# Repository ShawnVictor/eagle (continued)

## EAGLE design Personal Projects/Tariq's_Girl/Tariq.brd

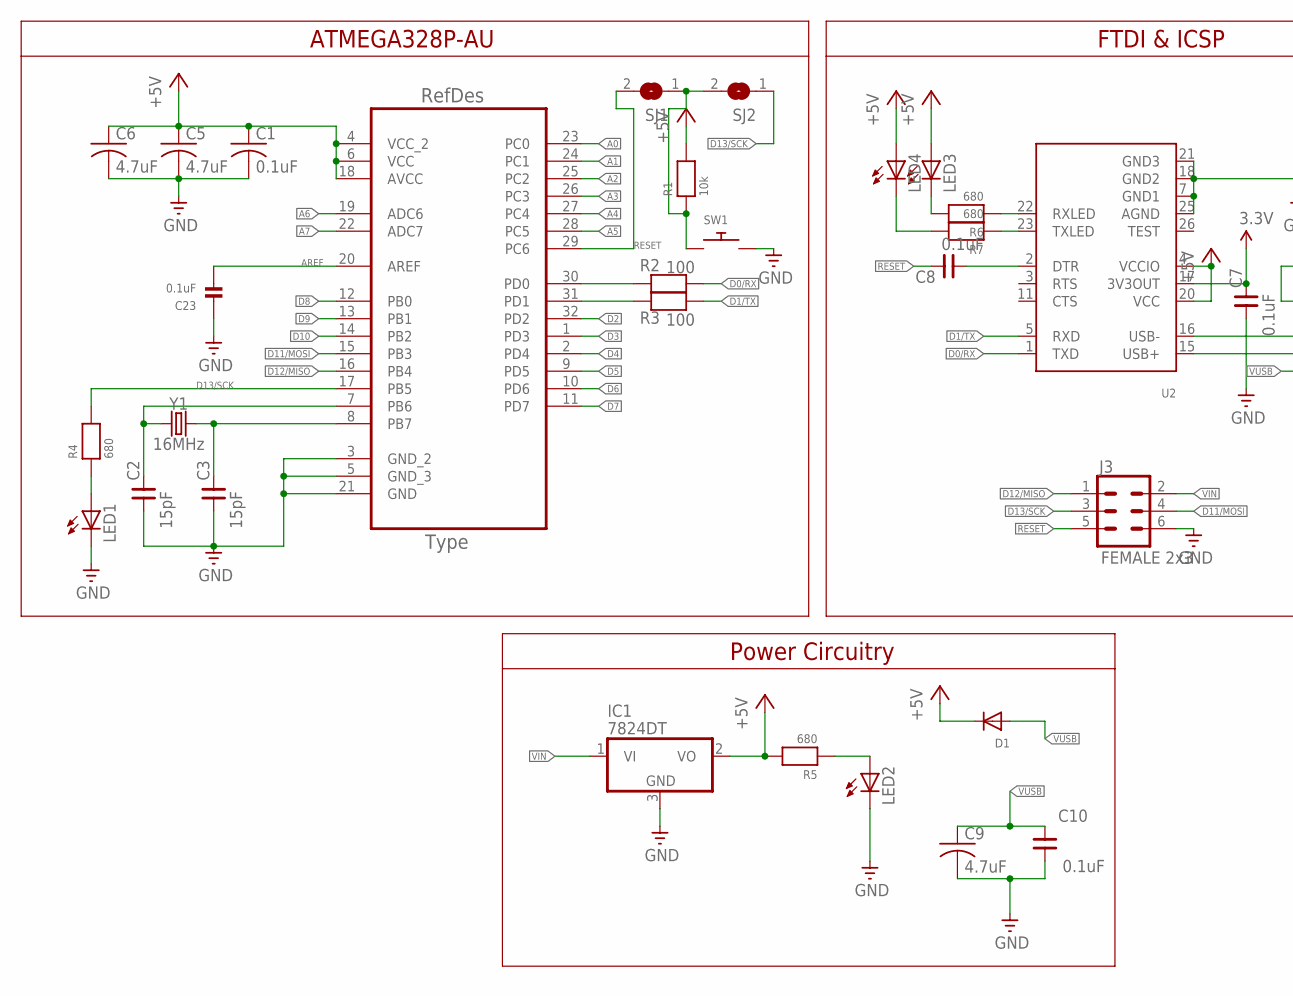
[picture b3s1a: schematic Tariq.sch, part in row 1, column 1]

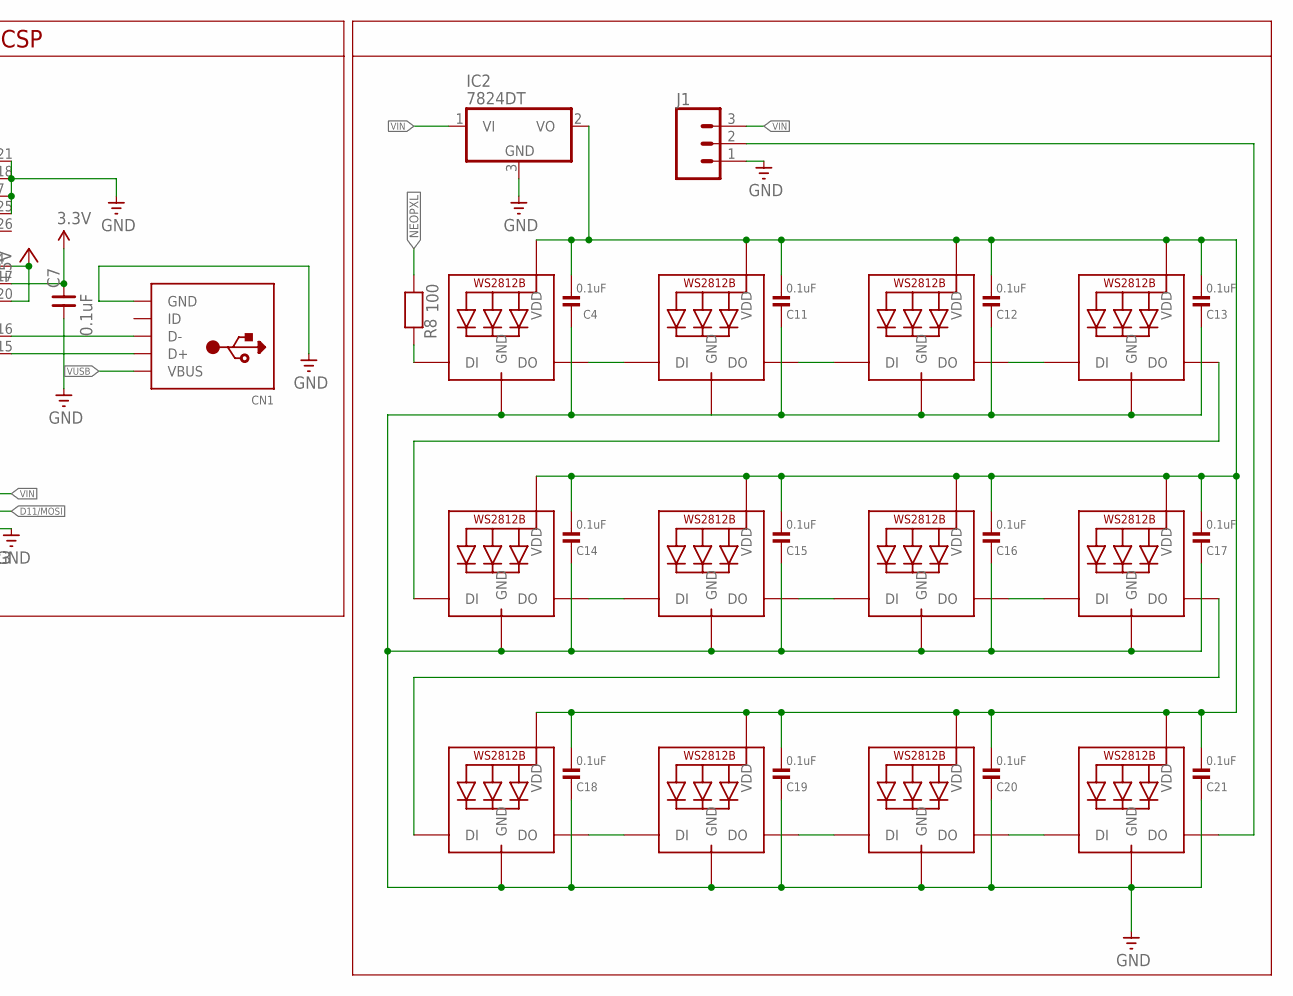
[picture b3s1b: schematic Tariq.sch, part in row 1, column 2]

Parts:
C1: 0.1uF; C0805
C2, C3: 15pF; 0805
C4, C11, C12, C13, C14, C15, C16, C17, C18, C19, C20, C21, C23: 0.1uF; 0603
C5, C6, C9: 4.7uF; C0805
C7, C8, C10: 0.1uF; 0805
CN1: USBMINIB; USB-MINIB
D1: DIODESOD-123; SOD-123
IC1, IC2: 7824DT; TO252
J1: CONN_03; 1X03
J3: FEMALE 2x3; 2X3
LED1, LED2, LED3, LED4: LEDCHIPLED_0805; CHIPLED_0805
LED5, LED6, LED7, LED8, LED9, LED10, LED11, LED12, LED13, LED14, LED15, LED16: WS2812B5050; WS2812B
R1: 10k; 0603
R2, R3, R8: 100; 0603
R4, R5, R6, R7: 680; 0603
SJ1, SJ2: SOLDERJUMPERWAVE; SOLDERJUMPER_WAVE
SW1: SWITCH_PUSHBUTTONEVQ-PE; TACT_PANA-EVQ
U1: ATMEGA328P-AU; QFP80P900X900X120-32N
U2: FT232RLSSOP28; SSOP28DB
Y1: 16MHz; HC49US

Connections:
3.3V: C7.2, U2.17 (3V3OUT)
+5V: C1.1, C5.1, C6.1, D1.C, IC1.2 (VO), LED3.A, LED4.A, R1.2, R5.2, U1.4 (VCC_2), U1.6 (VCC), U1.18 (AVCC), U2.4 (VCCIO), U2.20 (VCC)
A0: U1.23 (PC0)
A1: U1.24 (PC1)
A2: U1.25 (PC2)
A3: U1.26 (PC3)
A4: U1.27 (PC4)
A5: U1.28 (PC5)
A6: U1.19 (ADC6)
A7: U1.22 (ADC7)
AREF: C23.2, U1.20 (AREF)
D0/RX: R2.1, U2.1 (TXD)
D1/TX: R3.1, U2.5 (RXD)
D2: U1.32 (PD2)
D3: U1.1 (PD3)
D4: U1.2 (PD4)
D5: U1.9 (PD5)
D6: U1.10 (PD6)
D7: U1.11 (PD7)
D8: U1.12 (PB0)
D9: U1.13 (PB1)
D10: U1.14 (PB2)
D11/MOSI: J3.4, U1.15 (PB3)
D12/MISO: J3.1, U1.16 (PB4)
D13/SCK: J3.3, R4.2, SJ2.1, U1.17 (PB5)
GND: C1.2, C2.1, C3.1, C4.1, C5.2, C6.2, C7.1, C9.2, C10.1, C11.1, C12.1, C13.1, C14.1, C15.1, C16.1, C17.1, C18.1, C19.1, C20.1, C21.1, C23.1, CN1.GND, IC1.3 (GND), IC2.3 (GND), J1.1, J3.6, LED1.C, LED2.C, LED5.3-GND (GND), LED6.3-GND (GND), LED7.3-GND (GND), LED8.3-GND (GND), LED9.3-GND (GND), LED10.3-GND (GND), LED11.3-GND (GND), LED12.3-GND (GND), LED13.3-GND (GND), LED14.3-GND (GND), LED15.3-GND (GND), LED16.3-GND (GND), SW1.P$2, U1.3 (GND_2), U1.5 (GND_3), U1.21 (GND), U2.7 (GND1), U2.18 (GND2), U2.21 (GND3), U2.25 (AGND)
unnamed: C3.2, U1.8 (PB7), Y1.2
unnamed: C2.2, U1.7 (PB6), Y1.1
unnamed: LED2.A, R5.1
unnamed: CN1.D+, U2.15 (USB+)
unnamed: CN1.D-, U2.16 (USB-)
unnamed: R2.2, U1.30 (PD0)
unnamed: R3.2, U1.31 (PD1)
unnamed: LED3.C, R6.2
unnamed: LED1.A, R4.1
unnamed: LED5.2-DOUT (DO), LED6.4-DIN (DI)
unnamed: R6.1, U2.22 (RXLED)
unnamed: R7.1, U2.23 (TXLED)
unnamed: C8.1, U2.2 (DTR)
unnamed: LED4.C, R7.2
unnamed: LED6.2-DOUT (DO), LED7.4-DIN (DI)
unnamed: LED7.2-DOUT (DO), LED8.4-DIN (DI)
unnamed: LED8.2-DOUT (DO), LED9.4-DIN (DI)
unnamed: C4.2, C11.2, C12.2, C13.2, C14.2, C15.2, C16.2, C17.2, C18.2, C19.2, C20.2, C21.2, IC2.2 (VO), LED5.1-VDD (VDD), LED6.1-VDD (VDD), LED7.1-VDD (VDD), LED8.1-VDD (VDD), LED9.1-VDD (VDD), LED10.1-VDD (VDD), LED11.1-VDD (VDD), LED12.1-VDD (VDD), LED13.1-VDD (VDD), LED14.1-VDD (VDD), LED15.1-VDD (VDD), LED16.1-VDD (VDD)
unnamed: LED9.2-DOUT (DO), LED10.4-DIN (DI)
unnamed: LED10.2-DOUT (DO), LED11.4-DIN (DI)
unnamed: LED11.2-DOUT (DO), LED12.4-DIN (DI)
unnamed: LED12.2-DOUT (DO), LED13.4-DIN (DI)
unnamed: LED13.2-DOUT (DO), LED14.4-DIN (DI)
unnamed: LED14.2-DOUT (DO), LED15.4-DIN (DI)
unnamed: LED15.2-DOUT (DO), LED16.4-DIN (DI)
unnamed: LED5.4-DIN (DI), R8.2
unnamed: J1.2, LED16.2-DOUT (DO)
unnamed: R1.1, SJ1.1, SJ2.2, SW1.P$1
NEOPXL: R8.1
RESET: C8.2, J3.5, SJ1.2, U1.29 (PC6)
VIN: IC1.1 (VI), IC2.1 (VI), J1.3, J3.2
VUSB: C9.1, C10.2, CN1.VBUS, D1.A

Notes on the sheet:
ATMEGA328P-AU
FTDI & ICSP
Power Circuitry

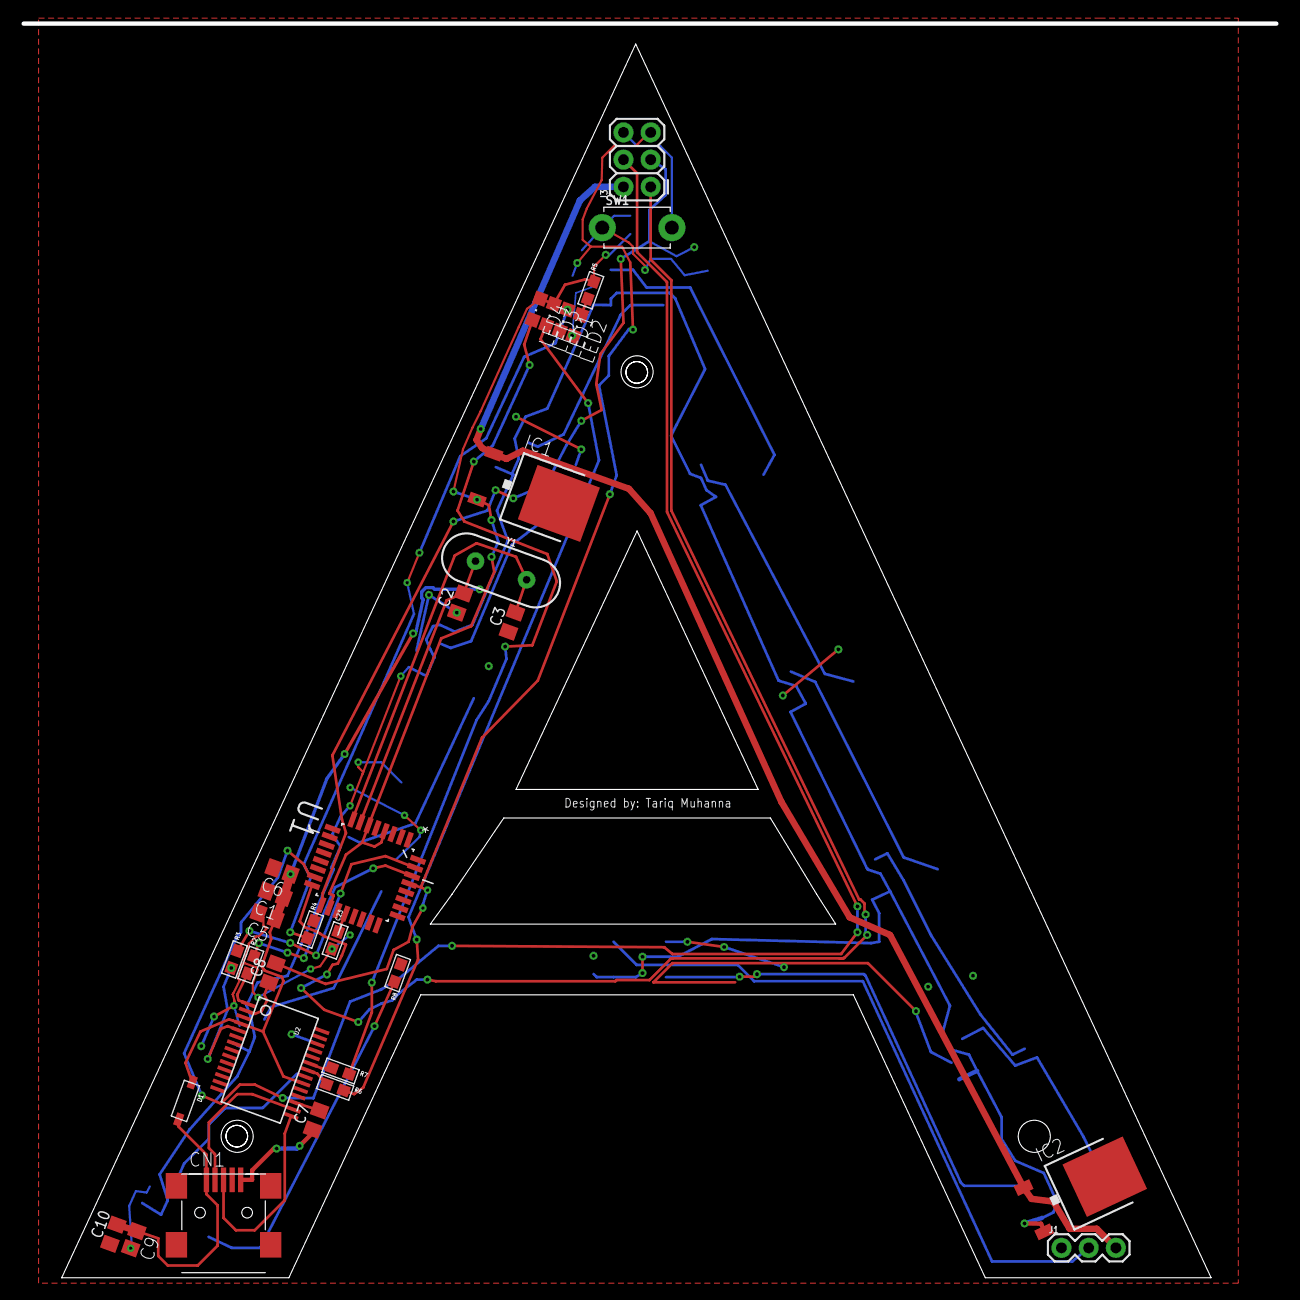
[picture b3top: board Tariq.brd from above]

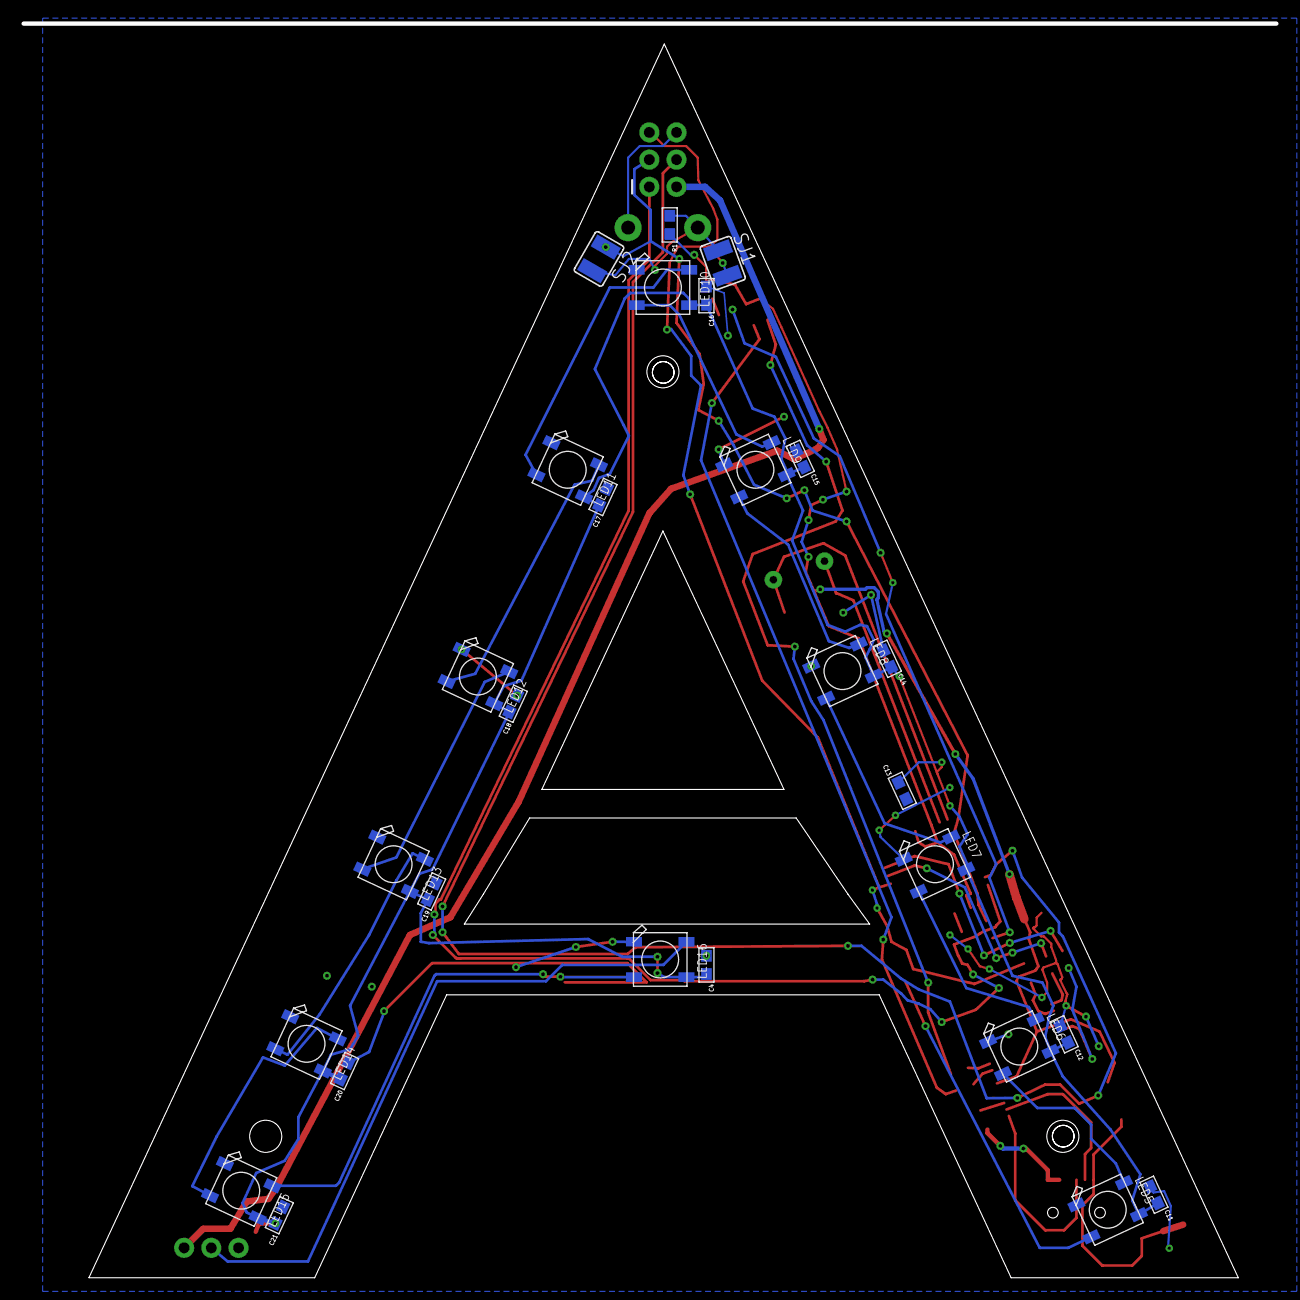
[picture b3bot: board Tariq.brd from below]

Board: 2 copper layers, 117.0 x 117.1 mm, 58 parts (27 on the bottom side), 40 nets.

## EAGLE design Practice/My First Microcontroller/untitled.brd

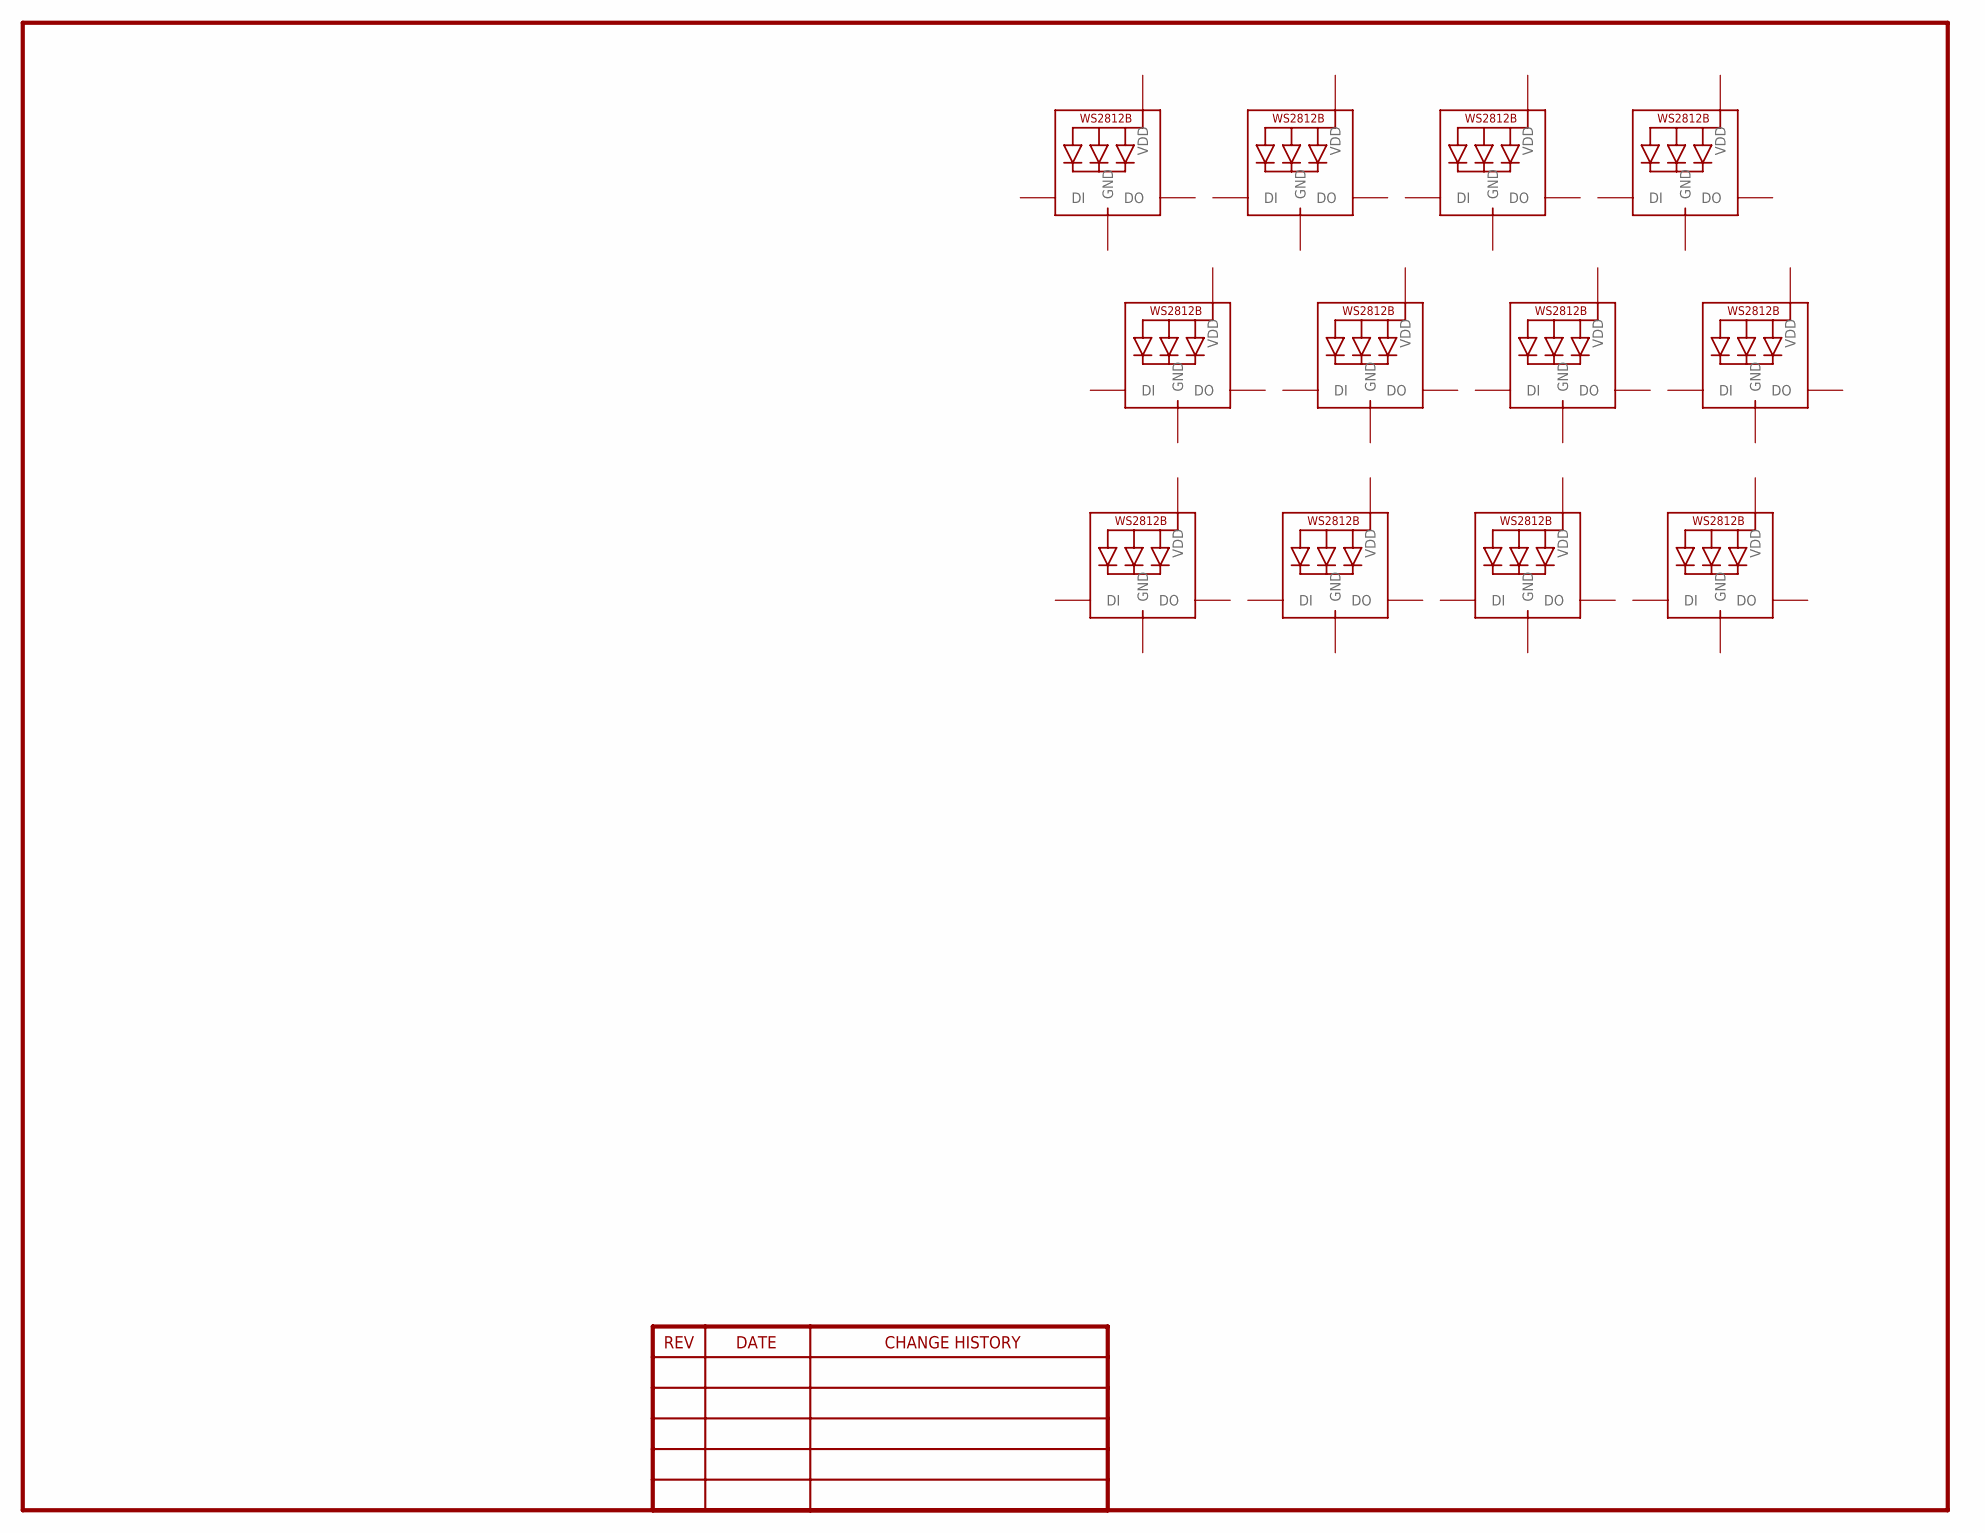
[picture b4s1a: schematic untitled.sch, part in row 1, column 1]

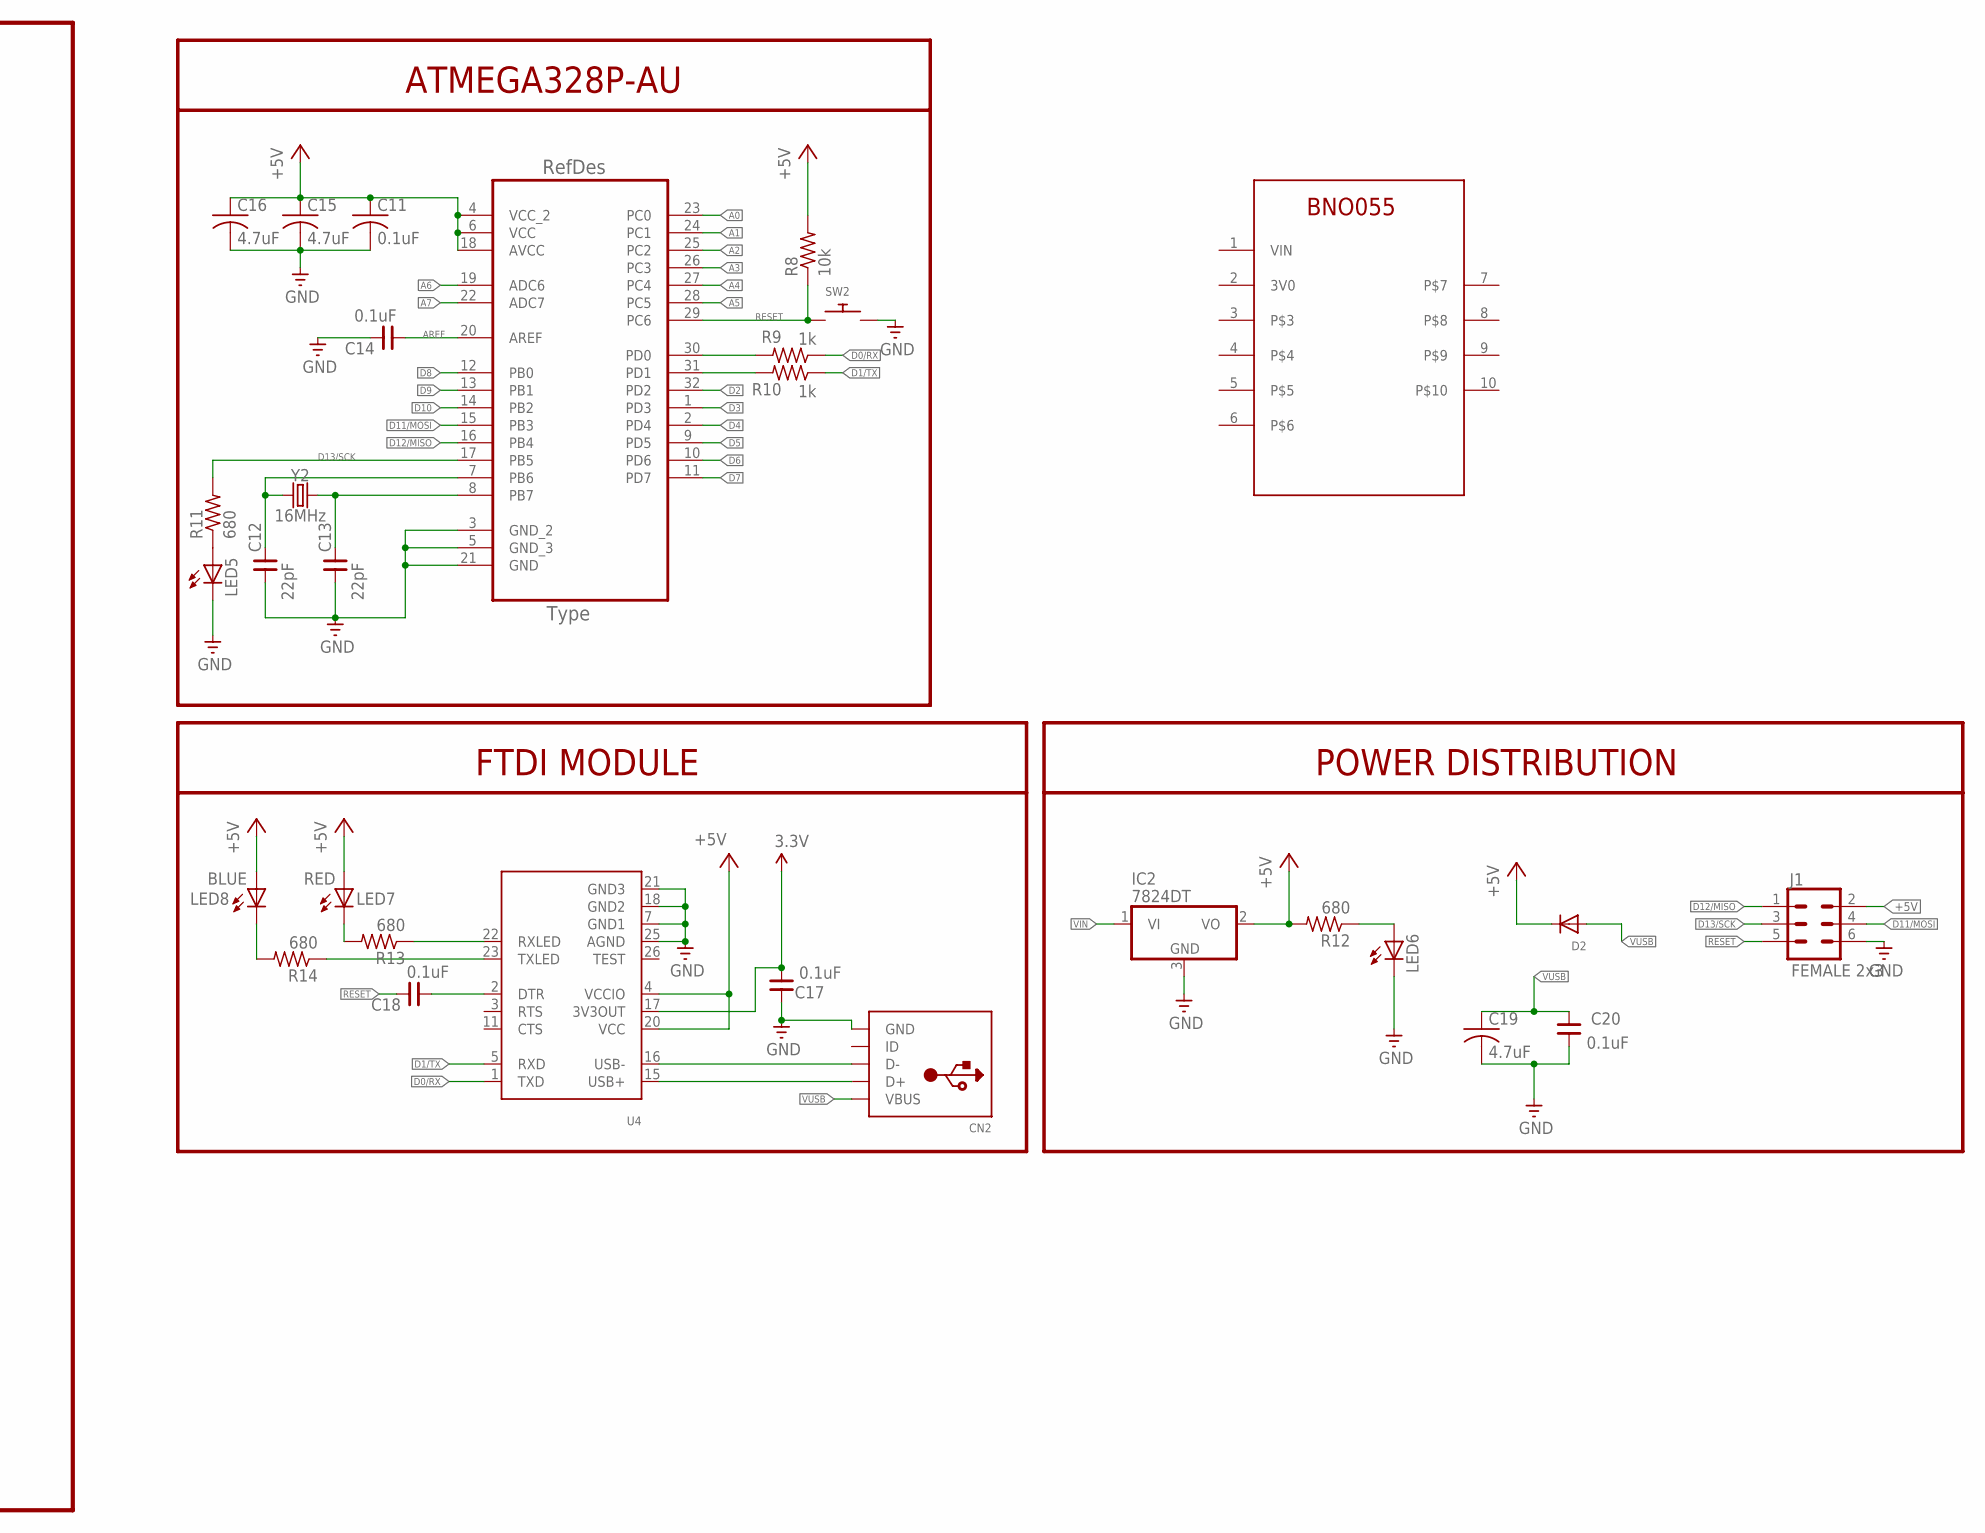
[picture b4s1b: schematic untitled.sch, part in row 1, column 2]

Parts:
C11: 0.1uF; C0805
C12, C13: 22pF; 0805
C14, C17, C18, C20: 0.1uF; 0805
C15, C16, C19: 4.7uF; C0805
CN2: USBMINIB; USB-MINIB
D2: DIODESOD-123; SOD-123
IC2: 7824DT; TO252
J1: FEMALE 2x3; 2X3
LED1, LED2, LED3, LED4, LED9, LED10, LED11, LED12, LED13, LED14, LED15, LED16: WS2812B5050; WS2812B
LED5, LED6: LEDCHIPLED_0805; CHIPLED_0805
LED7: RED; CHIPLED_0805
LED8: BLUE; CHIPLED_0805
R8: 10k; R0805
R9, R10: 1k; R0805
R11, R12, R13, R14: 680; R0805
SW2: SWITCH_PUSHBUTTONEVQ-PE; TACT_PANA-EVQ
U3: ATMEGA328P-AU; QFP80P900X900X120-32N
U4: FT232RLSSOP28; SSOP28DB
U$1: BNO055; BNO055_SHEILD
Y2: 16MHz; HC49US

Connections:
3.3V: C17.2, U4.17 (3V3OUT)
+5V: C11.1, C15.1, C16.1, D2.C, IC2.2 (VO), J1.2, LED7.A, LED8.A, R8.2, R12.2, U3.4 (VCC_2), U3.6 (VCC), U3.18 (AVCC), U4.4 (VCCIO), U4.20 (VCC)
A0: U3.23 (PC0)
A1: U3.24 (PC1)
A2: U3.25 (PC2)
A3: U3.26 (PC3)
A4: U3.27 (PC4)
A5: U3.28 (PC5)
A6: U3.19 (ADC6)
A7: U3.22 (ADC7)
AREF: C14.1, U3.20 (AREF)
D0/RX: R9.1, U4.1 (TXD)
D1/TX: R10.1, U4.5 (RXD)
D2: U3.32 (PD2)
D3: U3.1 (PD3)
D4: U3.2 (PD4)
D5: U3.9 (PD5)
D6: U3.10 (PD6)
D7: U3.11 (PD7)
D8: U3.12 (PB0)
D9: U3.13 (PB1)
D10: U3.14 (PB2)
D11/MOSI: J1.4, U3.15 (PB3)
D12/MISO: J1.1, U3.16 (PB4)
D13/SCK: J1.3, R11.2, U3.17 (PB5)
GND: C11.2, C12.1, C13.1, C14.2, C15.2, C16.2, C17.1, C19.2, C20.1, CN2.GND, IC2.3 (GND), J1.6, LED1.3-GND (GND), LED2.3-GND (GND), LED3.3-GND (GND), LED4.3-GND (GND), LED5.C, LED6.C, LED9.3-GND (GND), LED10.3-GND (GND), LED11.3-GND (GND), LED12.3-GND (GND), LED13.3-GND (GND), LED14.3-GND (GND), LED15.3-GND (GND), LED16.3-GND (GND), SW2.P$2, U3.3 (GND_2), U3.5 (GND_3), U3.21 (GND), U4.7 (GND1), U4.18 (GND2), U4.21 (GND3), U4.25 (AGND)
unnamed: LED5.A, R11.1
unnamed: C13.2, U3.8 (PB7), Y2.2
unnamed: C12.2, U3.7 (PB6), Y2.1
unnamed: R9.2, U3.30 (PD0)
unnamed: R10.2, U3.31 (PD1)
unnamed: LED6.A, R12.1
unnamed: CN2.D+, U4.15 (USB+)
unnamed: CN2.D-, U4.16 (USB-)
unnamed: R13.1, U4.22 (RXLED)
unnamed: R14.1, U4.23 (TXLED)
unnamed: LED8.C, R14.2
unnamed: LED7.C, R13.2
unnamed: C18.1, U4.2 (DTR)
RESET: C18.2, J1.5, R8.1, SW2.P$1, U3.29 (PC6)
VDD: LED1.1-VDD (VDD), LED2.1-VDD (VDD), LED3.1-VDD (VDD), LED4.1-VDD (VDD), LED9.1-VDD (VDD), LED10.1-VDD (VDD), LED11.1-VDD (VDD), LED12.1-VDD (VDD), LED13.1-VDD (VDD), LED14.1-VDD (VDD), LED15.1-VDD (VDD), LED16.1-VDD (VDD)
VIN: IC2.1 (VI)
VUSB: C19.1, C20.2, CN2.VBUS, D2.A

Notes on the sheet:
ATMEGA328P-AU
FTDI MODULE
POWER DISTRIBUTION

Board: 2 copper layers, 42 parts (0 on the bottom side), 25 nets, no tracks yet.

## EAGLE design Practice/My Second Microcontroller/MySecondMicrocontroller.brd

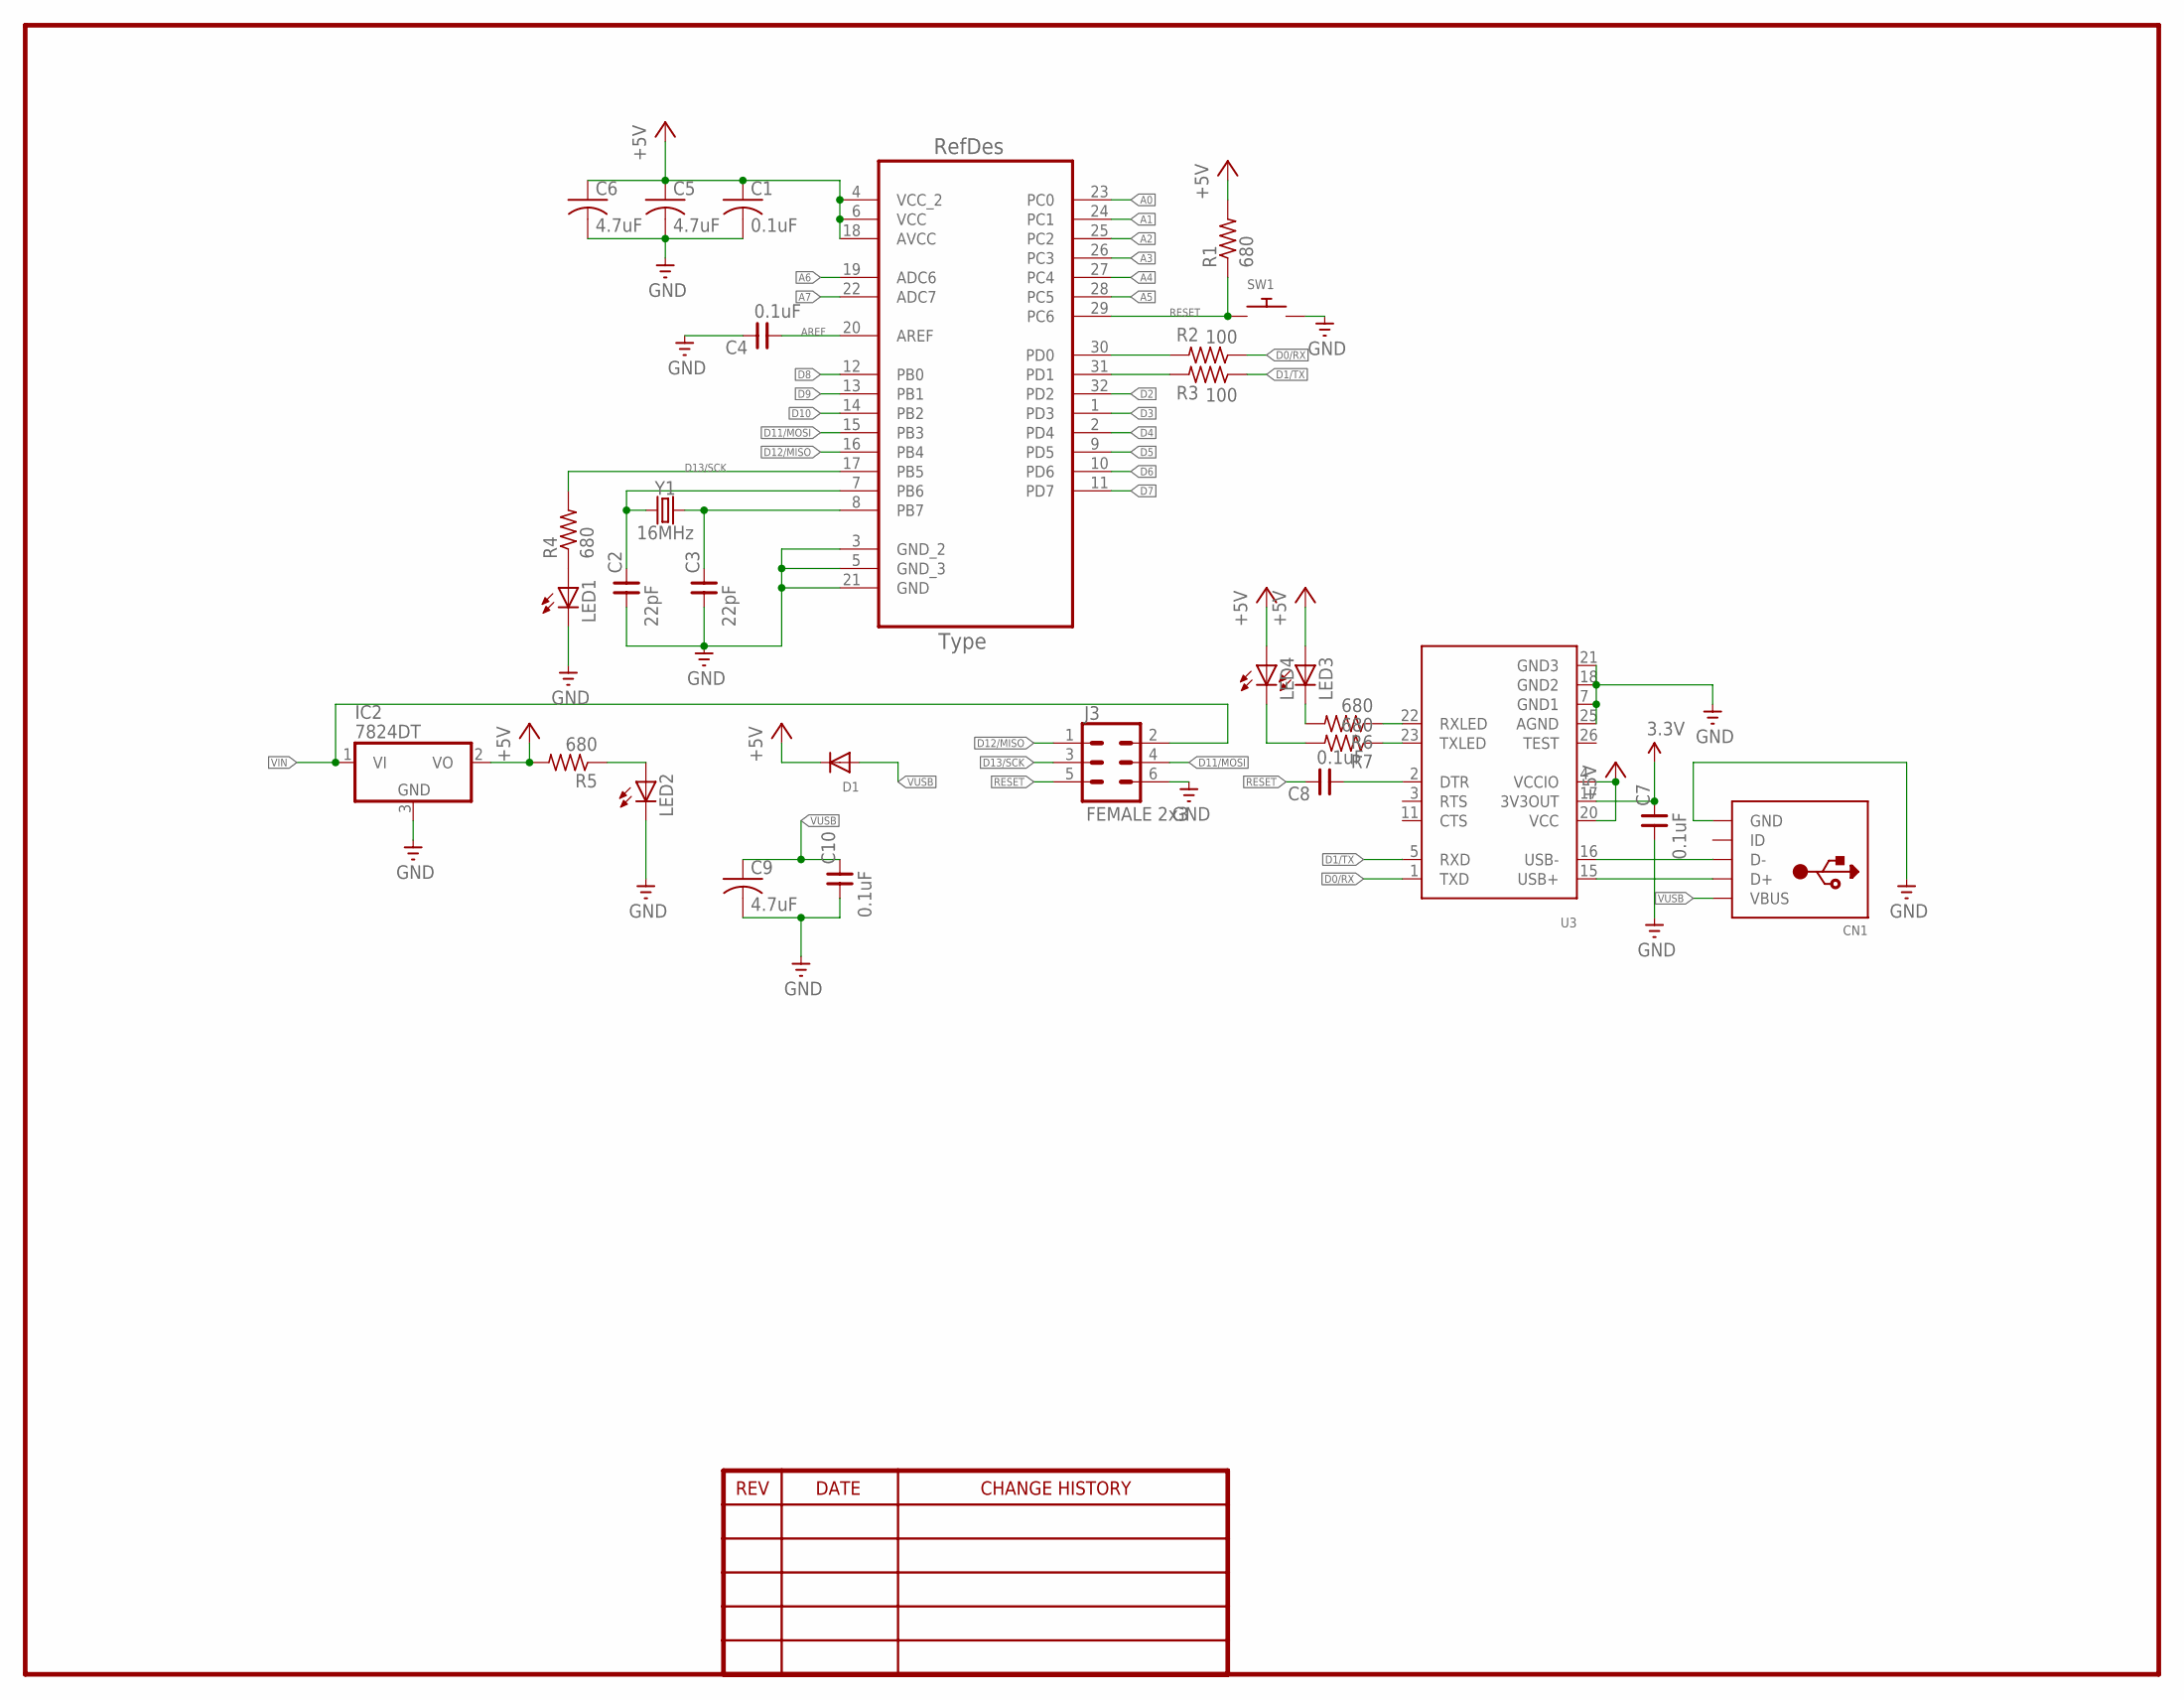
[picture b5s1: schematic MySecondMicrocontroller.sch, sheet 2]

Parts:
C1: 0.1uF; C0805
C2, C3: 22pF; 0805
C4, C7, C8, C10: 0.1uF; 0805
C5, C6, C9: 4.7uF; C0805
CN1: USBMINIB; USB-MINIB
D1: DIODESOD-123; SOD-123
IC2: 7824DT; TO252
J3: FEMALE 2x3; 2X3
LED1, LED2, LED3, LED4: LEDCHIPLED_0805; CHIPLED_0805
R1, R4, R5, R6, R7: 680; R0805
R2, R3: 100; R0805
SW1: SWITCH_PUSHBUTTONEVQ-PE; TACT_PANA-EVQ
U2: ATMEGA328P-AU; QFP80P900X900X120-32N
U3: FT232RLSSOP28; SSOP28DB
Y1: 16MHz; HC49US

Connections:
3.3V: C7.2, U3.17 (3V3OUT)
+5V: C1.1, C5.1, C6.1, D1.C, IC2.2 (VO), LED3.A, LED4.A, R1.2, R5.2, U2.4 (VCC_2), U2.6 (VCC), U2.18 (AVCC), U3.4 (VCCIO), U3.20 (VCC)
A0: U2.23 (PC0)
A1: U2.24 (PC1)
A2: U2.25 (PC2)
A3: U2.26 (PC3)
A4: U2.27 (PC4)
A5: U2.28 (PC5)
A6: U2.19 (ADC6)
A7: U2.22 (ADC7)
AREF: C4.1, U2.20 (AREF)
D0/RX: R2.1, U3.1 (TXD)
D1/TX: R3.1, U3.5 (RXD)
D2: U2.32 (PD2)
D3: U2.1 (PD3)
D4: U2.2 (PD4)
D5: U2.9 (PD5)
D6: U2.10 (PD6)
D7: U2.11 (PD7)
D8: U2.12 (PB0)
D9: U2.13 (PB1)
D10: U2.14 (PB2)
D11/MOSI: J3.4, U2.15 (PB3)
D12/MISO: J3.1, U2.16 (PB4)
D13/SCK: J3.3, R4.2, U2.17 (PB5)
GND: C1.2, C2.1, C3.1, C4.2, C5.2, C6.2, C7.1, C9.2, C10.1, CN1.GND, IC2.3 (GND), J3.6, LED1.C, LED2.C, SW1.P$2, U2.3 (GND_2), U2.5 (GND_3), U2.21 (GND), U3.7 (GND1), U3.18 (GND2), U3.21 (GND3), U3.25 (AGND)
unnamed: C3.2, U2.8 (PB7), Y1.2
unnamed: C2.2, U2.7 (PB6), Y1.1
unnamed: LED2.A, R5.1
unnamed: CN1.D+, U3.15 (USB+)
unnamed: CN1.D-, U3.16 (USB-)
unnamed: R2.2, U2.30 (PD0)
unnamed: R3.2, U2.31 (PD1)
unnamed: LED3.C, R6.2
unnamed: R6.1, U3.22 (RXLED)
unnamed: R7.1, U3.23 (TXLED)
unnamed: C8.1, U3.2 (DTR)
unnamed: LED4.C, R7.2
RESET: C8.2, J3.5, R1.1, SW1.P$1, U2.29 (PC6)
VIN: IC2.1 (VI), J3.2
VUSB: C9.1, C10.2, CN1.VBUS, D1.A

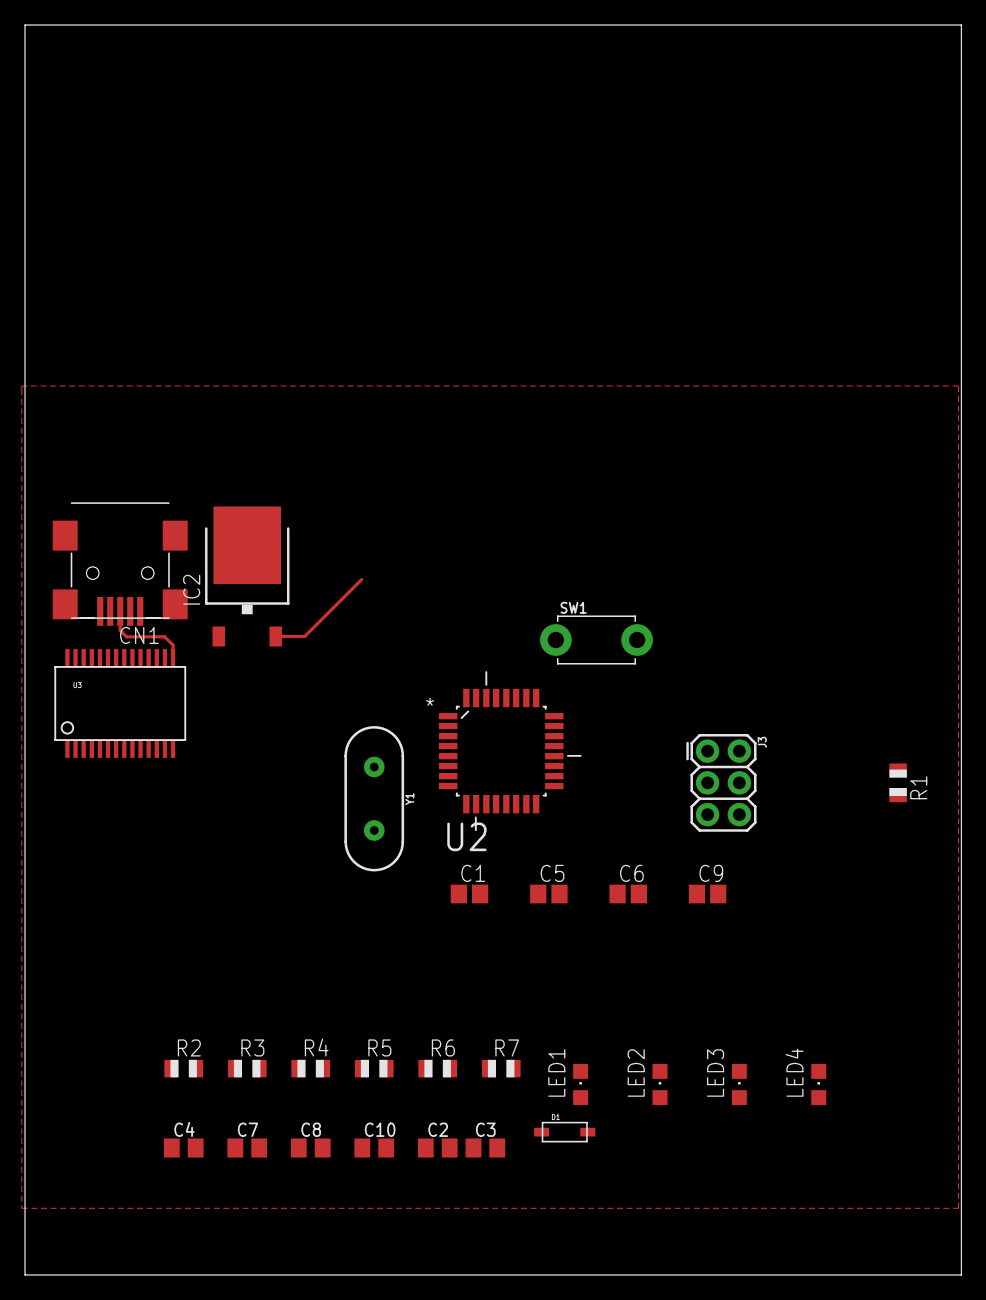
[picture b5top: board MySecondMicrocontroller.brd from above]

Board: 2 copper layers, 74.9 x 100.0 mm, 29 parts (0 on the bottom side), 24 nets.
